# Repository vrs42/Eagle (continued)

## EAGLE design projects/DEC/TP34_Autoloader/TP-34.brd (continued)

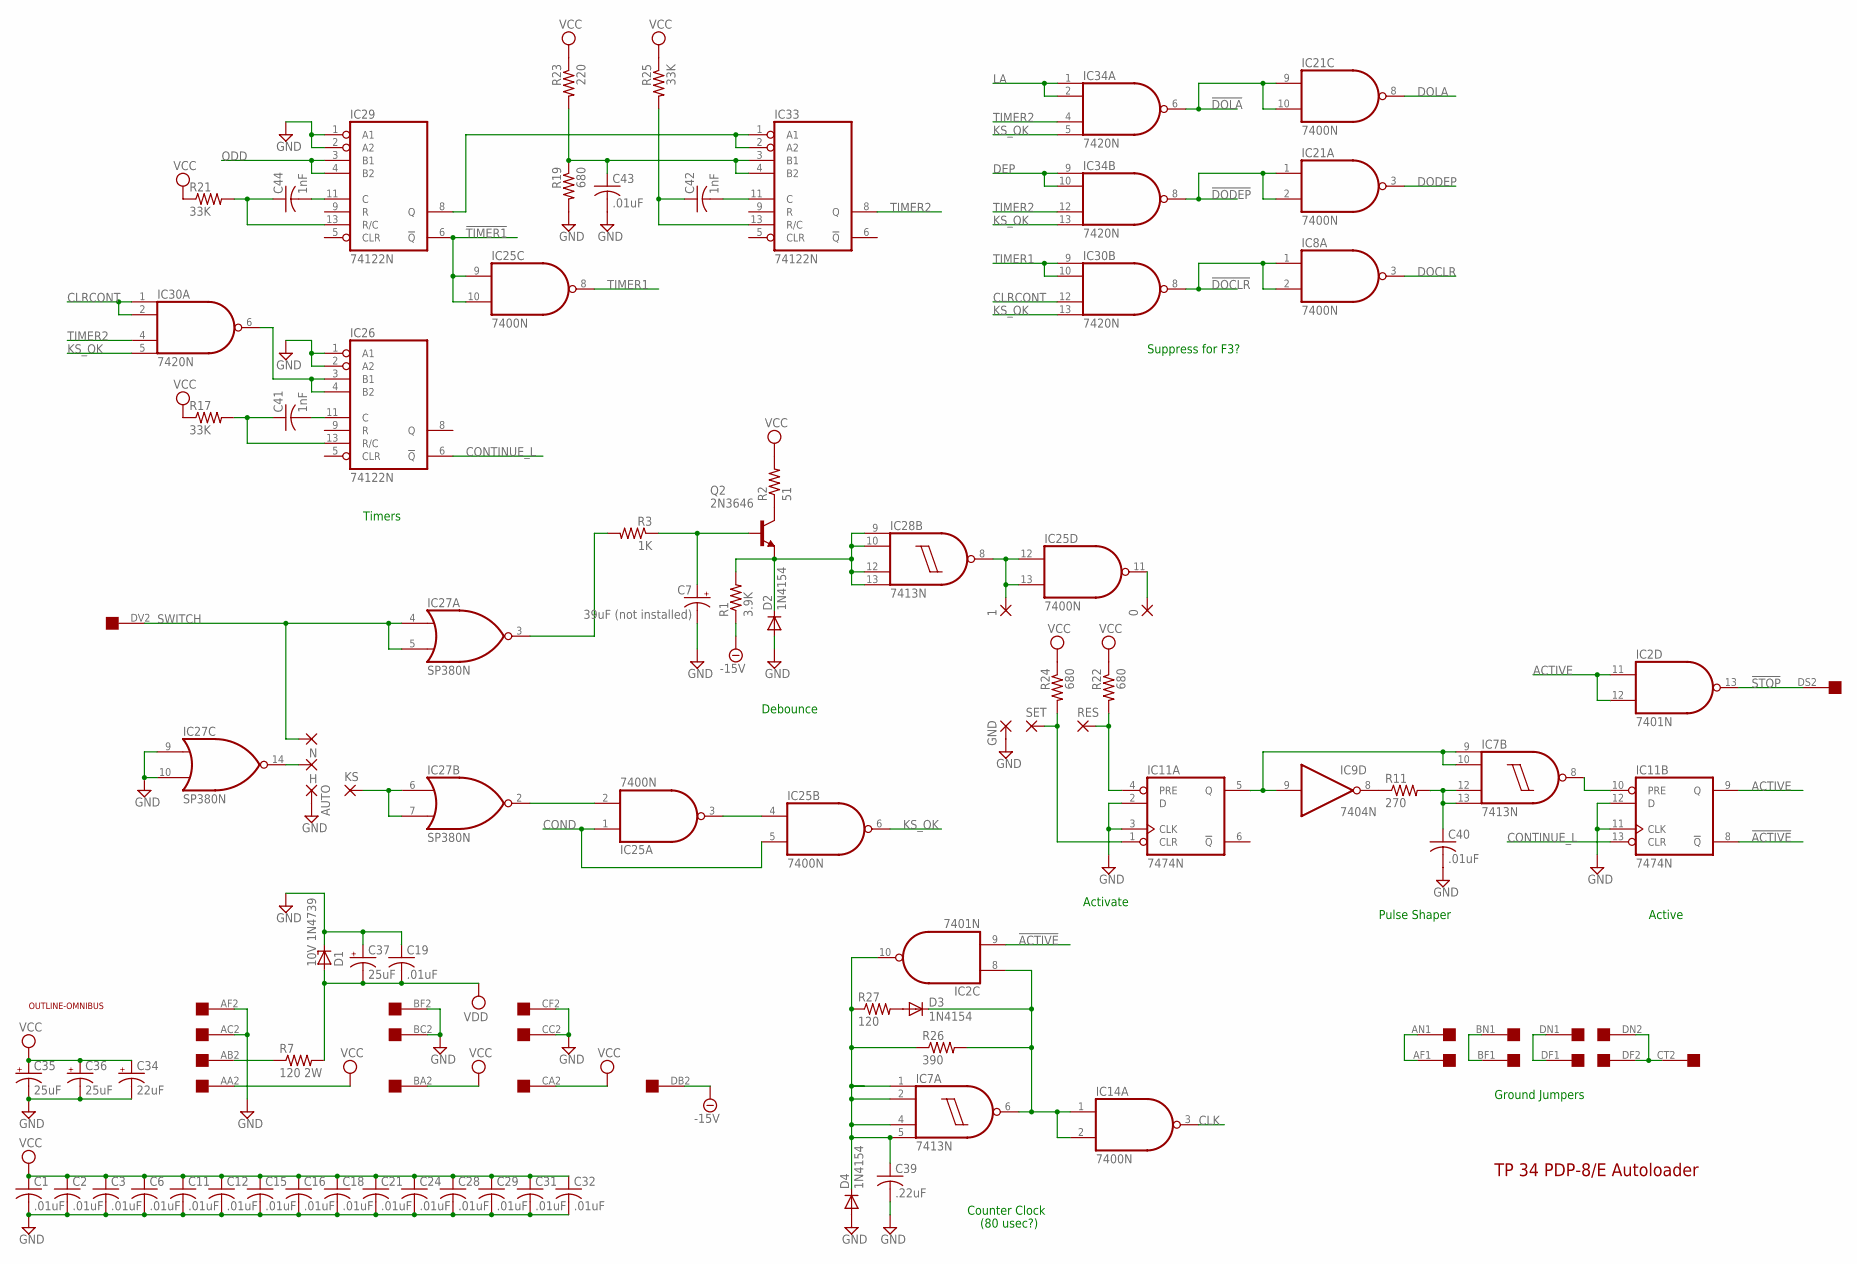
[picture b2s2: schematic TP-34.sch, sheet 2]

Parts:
0, 1: 1,6/0,8
AUTO: 1,6/0,8
C1, C2, C3, C6, C11, C12, C15, C16, C18, C19, C21, C24, C28, C29, C31, C32, C40, C43: .01uF; C075-032X103
C7: 39uF (not installed); E15-5
C34: 22uF; E12-8
C35, C36, C37: 25uF; E15-5
C39: .22uF; C075-032X103
C41, C42, C44: 1nF; C075-032X103
D1: 10V 1N4739; C1702-15
D2, D3, D4: 1N4154; DO35-10
GND: 1,6/0,8
H: 1,6/0,8
IC2: 7401N; DIL14
IC7, IC28: 7413N; DIL14
IC8, IC14, IC21, IC25: 7400N; DIL14
IC9: 7404N; DIL14
IC11: 7474N; DIL14
IC26, IC29, IC33: 74122N; DIL14
IC27: SP380N; DIL14
IC30, IC34: 7420N; DIL14
KS: 1,6/0,8
N: 1,6/0,8
Q2: 2N3646; TO5
R1: 3.9K; 0207/10
R2: 51; 0207/10
R3: 1K; 0207/10
R7: 120 2W; 0414/15
R11: 270; 0207/12
R17, R21, R25: 33K; 0207/10
R19, R22, R24: 680; 0207/10
R23: 220; 0207/10
R26: 390; 0207/10
R27: 120; 0207/10
RES: 1,6/0,8
SET: 1,6/0,8
U$1: OUTLINE-OMNIBUS; OMNIBUS
U$2: QUAD; EDGE-CON8

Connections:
!ACTIVE: IC2.9 (I1), IC11.8 (!Q); also elsewhere on the board
!DOCLR: IC8.1 (I0), IC8.2 (I1), IC30.8 (O); also elsewhere on the board
!DODEP: IC21.1 (I0), IC21.2 (I1), IC34.8 (O); also elsewhere on the board
!DOLA: IC21.9 (I0), IC21.10 (I1), IC34.6 (O); also elsewhere on the board
!STOP: IC2.13 (O), U$2.DS2
!TIMER1: IC25.9 (I0), IC25.10 (I1), IC29.6 (!Q)
-15V: R1.1, U$2.DB2
ACTIVE: IC2.11 (I0), IC2.12 (I1), IC11.9 (Q); also elsewhere on the board
CLK: IC14.3 (O); also elsewhere on the board
CLRCONT: IC30.1 (I0), IC30.2 (I1), IC30.12 (I2); also elsewhere on the board
COND: IC25.1 (I0), IC25.5 (I1); also elsewhere on the board
CONTINUE_L: IC11.13 (CLR), IC26.6 (!Q); also elsewhere on the board
DEP: IC34.9 (I0), IC34.10 (I1); also elsewhere on the board
DOCLR: IC8.3 (O); also elsewhere on the board
DODEP: IC21.3 (O); also elsewhere on the board
DOLA: IC21.8 (O); also elsewhere on the board
GND: AUTO.1, C1.2, C2.2, C3.2, C6.2, C7.-, C11.2, C12.2, C15.2, C16.2, C18.2, C19.1, C21.2, C24.2, C28.2, C29.2, C31.2, C32.2, C34.-, C35.-, C36.-, C37.+, C39.2, C40.2, C43.2, D1.C, D2.A, D4.A, GND.1, IC2.7 (GND), IC7.7 (GND), IC8.7 (GND), IC9.7 (GND), IC11.2 (D), IC11.3 (CLK), IC11.7 (GND), IC11.11 (CLK), IC11.12 (D), IC14.7 (GND), IC21.7 (GND), IC25.7 (GND), IC26.1 (A1), IC26.2 (A2), IC26.7 (GND), IC27.1 (GND), IC27.9 (I0), IC27.10 (I1), IC28.7 (GND), IC29.1 (A1), IC29.2 (A2), IC29.7 (GND), IC30.7 (GND), IC33.7 (GND), IC34.7 (GND), R19.2, U$2.AC2, U$2.AF2, U$2.BC2, U$2.BF2, U$2.CC2, U$2.CF2; also elsewhere on the board
KS_OK: IC25.6 (O), IC30.5 (I3), IC30.13 (I3), IC34.5 (I3), IC34.13 (I3)
LA: IC34.1 (I0), IC34.2 (I1); also elsewhere on the board
unnamed: U$2.AF1, U$2.AN1
unnamed: U$2.BF1, U$2.BN1
unnamed: U$2.DF1, U$2.DN1
unnamed: U$2.CT2, U$2.DF2, U$2.DN2
unnamed: D2.C, IC28.9 (I0), IC28.10 (I1), IC28.12 (I2), IC28.13 (I3), Q2.1 (E), R1.2
unnamed: D3.C, IC2.8 (I0), IC7.6 (O), IC14.1 (I0), IC14.2 (I1), R26.2
unnamed: D3.A, R27.2
unnamed: C39.1, D4.C, IC2.10 (O), IC7.1 (I0), IC7.2 (I1), IC7.4 (I2), IC7.5 (I3), R26.1, R27.1
unnamed: IC7.9 (I0), IC7.10 (I1), IC9.9 (I), IC11.5 (Q)
unnamed: 1.1, IC25.12 (I0), IC25.13 (I1), IC28.8 (O)
unnamed: IC11.4 (PRE), R22.2, RES.1
unnamed: IC11.1 (CLR), R24.2, SET.1
unnamed: 0.1, IC25.11 (O)
unnamed: C42.1, IC33.13 (R/C), R25.2
unnamed: C42.2, IC33.11 (C)
unnamed: C43.1, IC33.3 (B1), IC33.4 (B2), R19.1, R23.2
unnamed: C44.1, IC29.13 (R/C), R21.2
unnamed: C40.1, IC7.12 (I2), IC7.13 (I3), R11.2
unnamed: IC7.8 (O), IC11.10 (PRE)
unnamed: C44.2, IC29.11 (C)
unnamed: IC9.8 (O), R11.1
unnamed: C7.+, Q2.2 (B), R3.1
unnamed: Q2.3 (C), R2.1
unnamed: C41.1, IC26.13 (R/C), R17.2
unnamed: C41.2, IC26.11 (C)
unnamed: R7.1, U$2.AB2
unnamed: IC25.3 (O), IC25.4 (I0)
unnamed: IC25.2 (I1), IC27.2 (O)
unnamed: IC26.3 (B1), IC26.4 (B2), IC30.6 (O)
unnamed: IC27.6 (I0), IC27.7 (I1), KS.1
unnamed: H.1, IC27.14 (O)
unnamed: IC29.8 (Q), IC33.1 (A1), IC33.2 (A2)
ODD: IC29.3 (B1), IC29.4 (B2); also elsewhere on the board
SWITCH: IC27.4 (I0), IC27.5 (I1), N.1, U$2.DV2
SWITCHL: IC27.3 (O), R3.2
TIMER1: IC25.8 (O), IC30.9 (I0), IC30.10 (I1)
TIMER2: IC30.4 (I2), IC33.8 (Q), IC34.4 (I2), IC34.12 (I2)
VCC: C1.1, C2.1, C3.1, C6.1, C11.1, C12.1, C15.1, C16.1, C18.1, C21.1, C24.1, C28.1, C29.1, C31.1, C32.1, C34.+, C35.+, C36.+, IC2.14 (VCC), IC7.14 (VCC), IC8.14 (VCC), IC9.14 (VCC), IC11.14 (VCC), IC14.14 (VCC), IC21.14 (VCC), IC25.14 (VCC), IC26.14 (VCC), IC27.8 (VCC), IC28.14 (VCC), IC29.14 (VCC), IC30.14 (VCC), IC33.14 (VCC), IC34.14 (VCC), R2.2, R17.1, R21.1, R22.1, R23.1, R24.1, R25.1, U$2.AA2, U$2.BA2, U$2.CA2; also elsewhere on the board
VDD: C19.2, C37.-, D1.A, R7.2; also elsewhere on the board

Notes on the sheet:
TP 34 PDP-8/E Autoloader
Counter Clock
Pulse Shaper
Activate
Active
Ground Jumpers
Timers
Suppress for F3?
Debounce
(80 usec?)

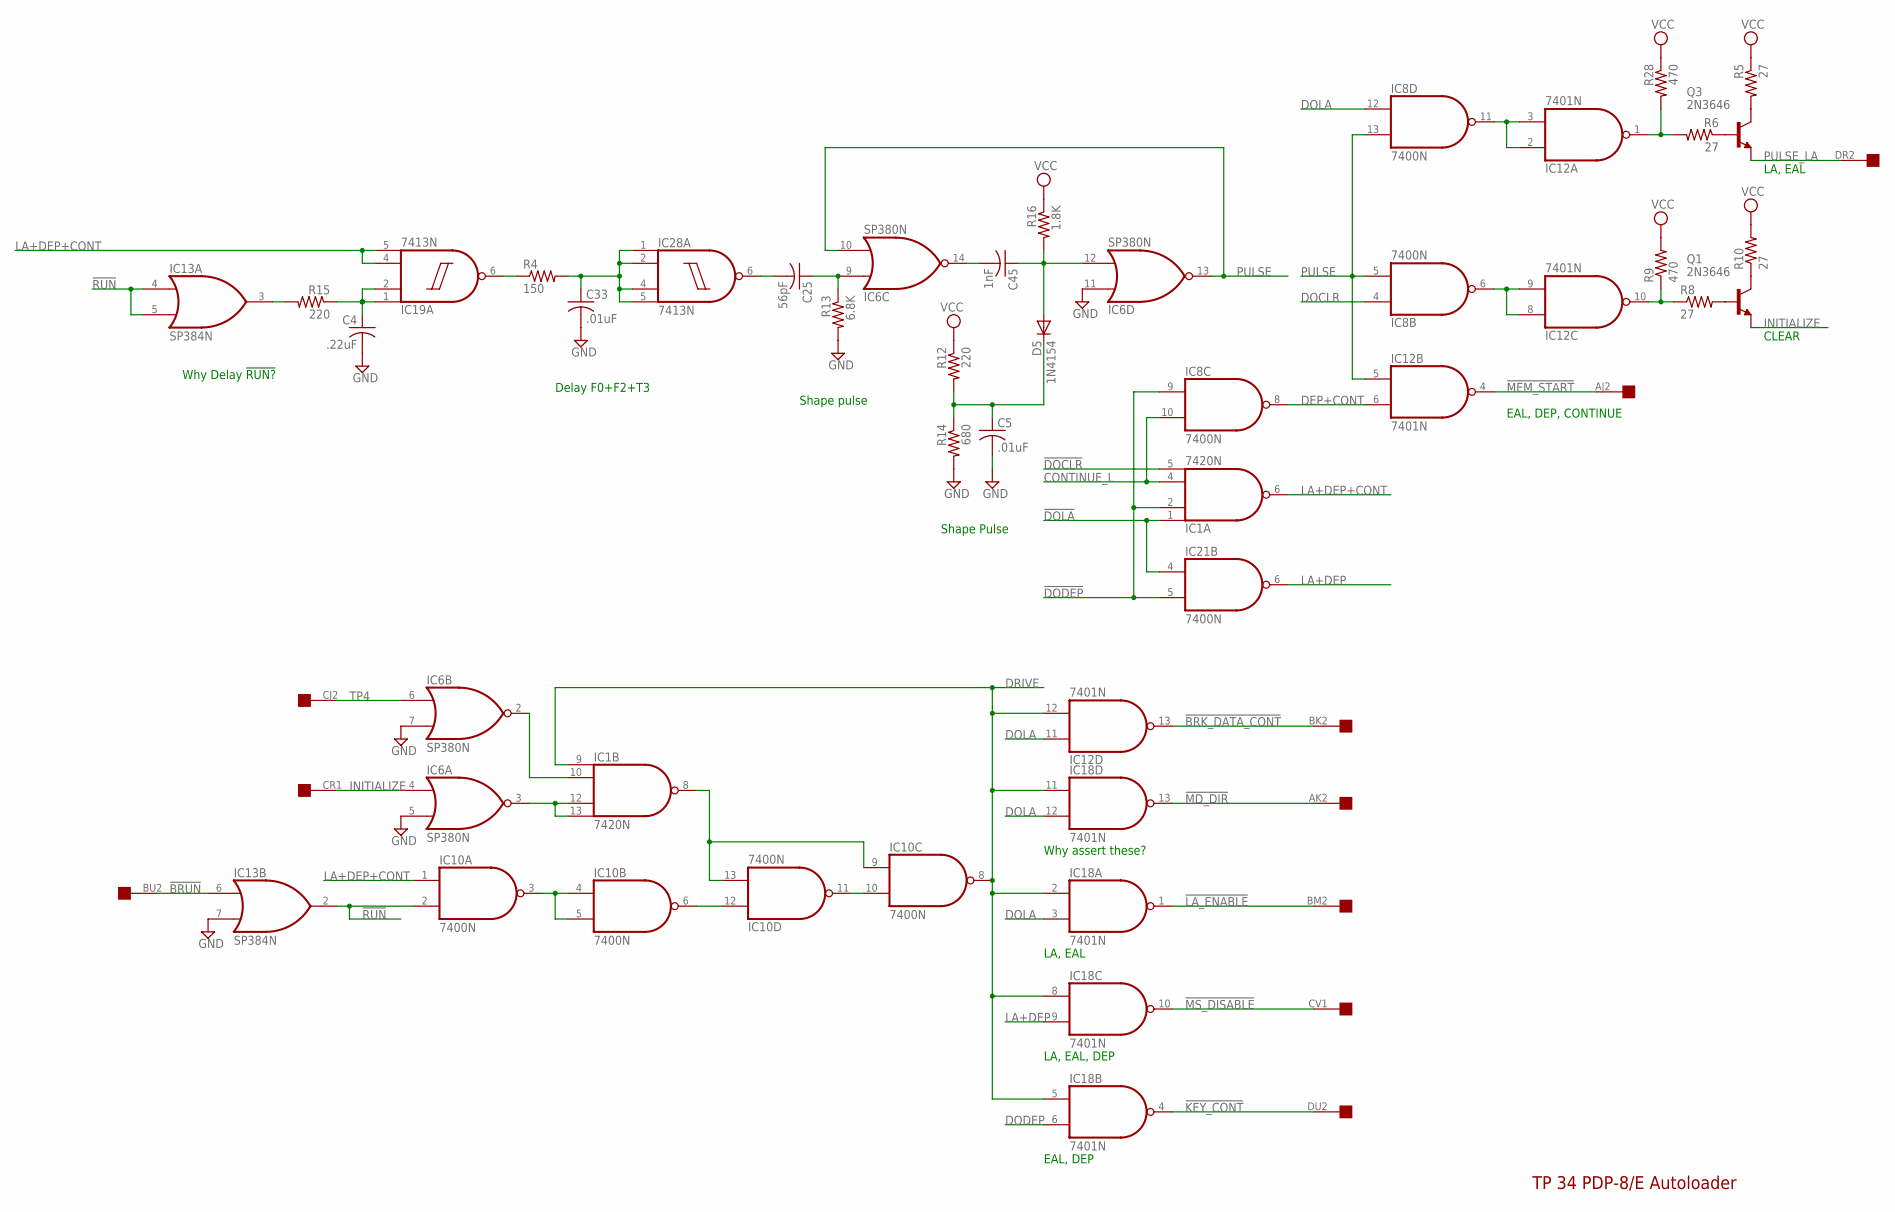
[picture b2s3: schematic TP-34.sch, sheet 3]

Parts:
C4: .22uF; C075-032X103
C5, C33: .01uF; C075-032X103
C25: 56pF; C102-043X133
C45: 1nF; C050-035X075
D5: 1N4154; DO35-10
IC1: 7420N; DIL14
IC6: SP380N; DIL14
IC8, IC10, IC21: 7400N; DIL14
IC12, IC18: 7401N; DIL14
IC13: SP384N; DIL14
IC19, IC28: 7413N; DIL14
Q1, Q3: 2N3646; TO5
R4: 150; 0207/10
R5, R6, R8, R10: 27; 0207/10
R9, R28: 470; 0207/10
R12: 220; 0207/10
R13: 6.8K; 0207/10
R14: 680; 0207/10
R15: 220; 0207/15
R16: 1.8K; 0207/10
U$2: QUAD; EDGE-CON8

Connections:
!BRK_DATA_CONT: IC12.13 (O), U$2.BK2
!BRUN: IC13.6 (I0), U$2.BU2
!DOCLR: IC1.5 (I3); also elsewhere on the board
!DODEP: IC1.2 (I1), IC8.9 (I0), IC21.5 (I1); also elsewhere on the board
!DOLA: IC1.1 (I0), IC21.4 (I0); also elsewhere on the board
!INITIALIZE: IC1.12 (I2), IC1.13 (I3), IC6.3 (O)
!KEY_CONT: IC18.4 (O), U$2.DU2
!LA_ENABLE: IC18.1 (O), U$2.BM2
!MD_DIR: IC18.13 (O), U$2.AK2
!MEM_START: IC12.4 (O), U$2.AJ2
!MS_DISABLE: IC18.10 (O), U$2.CV1
!RUN: IC10.2 (I1), IC13.2 (O), IC13.4 (I0), IC13.5 (I1)
!TP4: IC1.10 (I1), IC6.2 (O)
BRUNL: IC13.3 (O), R15.2
CONTINUE_L: IC1.4 (I2), IC8.10 (I1); also elsewhere on the board
DEP+CONT: IC8.8 (O), IC12.6 (I1)
DOCLR: IC8.4 (I0); also elsewhere on the board
DODEP: IC18.6 (I1); also elsewhere on the board
DOLA: IC8.12 (I0), IC12.11 (I0), IC18.3 (I1), IC18.12 (I1); also elsewhere on the board
DRIVE: IC1.9 (I0), IC10.8 (O), IC12.12 (I1), IC18.2 (I0), IC18.5 (I0), IC18.8 (I0), IC18.11 (I0); also elsewhere on the board
GND: C4.2, C5.2, C33.2, IC1.7 (GND), IC6.1 (GND), IC6.5 (I1), IC6.7 (I1), IC6.11 (I0), IC8.7 (GND), IC10.7 (GND), IC12.7 (GND), IC13.1 (GND), IC13.7 (I1), IC18.7 (GND), IC19.7 (GND), IC21.7 (GND), IC28.7 (GND), R13.2, R14.2; also elsewhere on the board
INITIALIZE: IC6.4 (I0), Q1.1 (E), U$2.CR1
LA+DEP: IC18.9 (I1), IC21.6 (O); also elsewhere on the board
LA+DEP+CONT: IC1.6 (O), IC10.1 (I0), IC19.4 (I2), IC19.5 (I3)
unnamed: IC10.6 (O), IC10.12 (I0)
unnamed: C25.2, IC28.6 (O)
unnamed: C25.1, IC6.9 (I0), R13.1
unnamed: C45.1, D5.A, IC6.12 (I1), R16.2
unnamed: C5.1, D5.C, R12.2, R14.1
unnamed: C45.2, IC6.14 (O)
unnamed: IC1.8 (O), IC10.9 (I0), IC10.13 (I1)
unnamed: IC8.11 (O), IC12.2 (I0), IC12.3 (I1)
unnamed: IC8.6 (O), IC12.8 (I0), IC12.9 (I1)
unnamed: IC10.3 (O), IC10.4 (I0), IC10.5 (I1)
unnamed: IC10.10 (I1), IC10.11 (O)
unnamed: IC12.1 (O), R6.2, R28.2
unnamed: IC12.10 (O), R8.1, R9.1
unnamed: Q1.3 (C), R10.1
unnamed: Q1.2 (B), R8.2
unnamed: C4.1, IC19.1 (I0), IC19.2 (I1), R15.1
unnamed: IC19.6 (O), R4.1
unnamed: C33.1, IC28.1 (I0), IC28.2 (I1), IC28.4 (I2), IC28.5 (I3), R4.2
unnamed: Q3.3 (C), R5.2
unnamed: Q3.2 (B), R6.1
PULSE: IC6.10 (I1), IC6.13 (O), IC8.5 (I1), IC8.13 (I1), IC12.5 (I0)
PULSE_LA: Q3.1 (E), U$2.DR2
TP4: IC6.6 (I0), U$2.CJ2
VCC: IC1.14 (VCC), IC6.8 (VCC), IC8.14 (VCC), IC10.14 (VCC), IC12.14 (VCC), IC13.8 (VCC), IC18.14 (VCC), IC19.14 (VCC), IC21.14 (VCC), IC28.14 (VCC), R5.1, R9.2, R10.2, R12.1, R16.1, R28.1; also elsewhere on the board

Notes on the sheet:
Why Delay !RUN?
Delay F0+F2+T3
Shape Pulse
TP 34 PDP-8/E Autoloader
Shape pulse
Why assert these?
LA, EAL
LA, EAL, DEP
EAL, DEP
CLEAR
EAL, DEP, CONTINUE

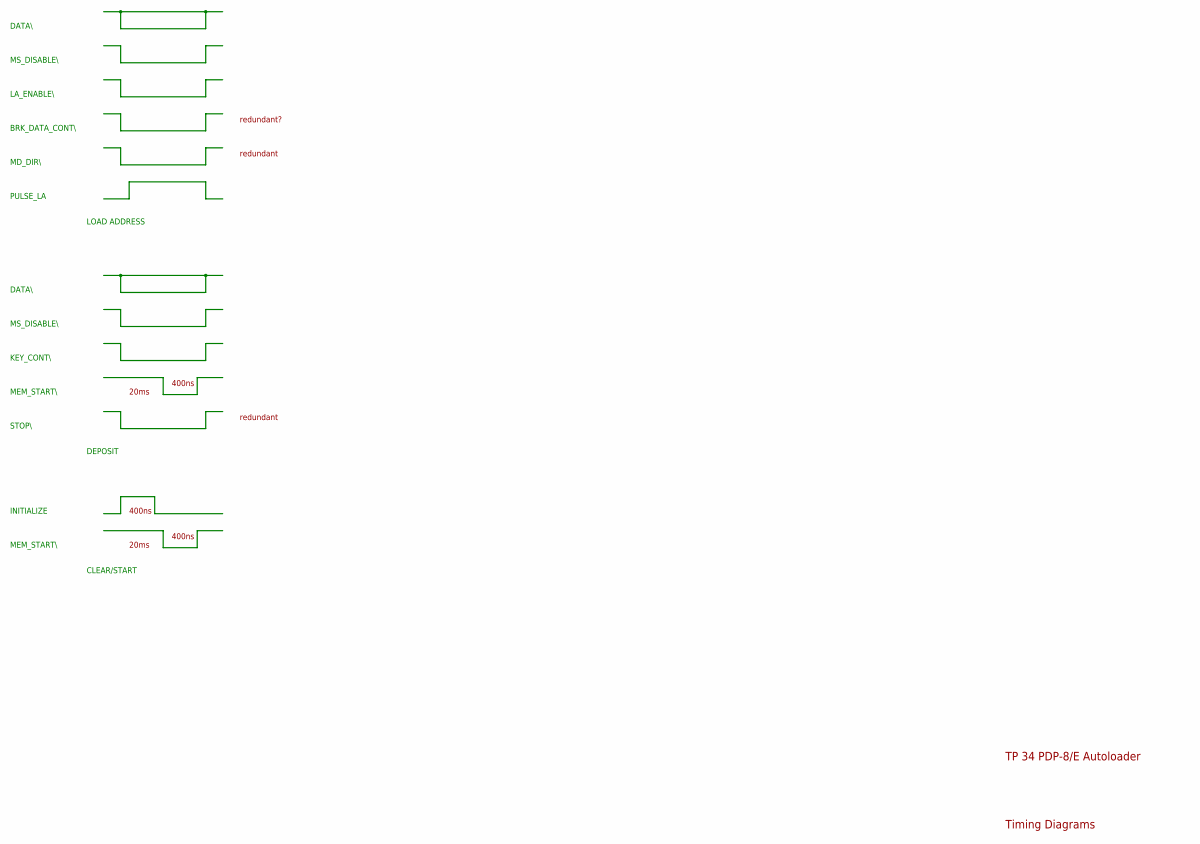
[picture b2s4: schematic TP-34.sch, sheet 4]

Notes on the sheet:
DATA\\
MS_DISABLE\\
BRK_DATA_CONT\\
MD_DIR\\
LOAD ADDRESS
MEM_START\\
KEY_CONT\\
DEPOSIT
PULSE_LA
STOP\\
INITIALIZE
TP 34 PDP-8/E Autoloader
Timing Diagrams
LA_ENABLE\\
CLEAR/START
redundant
20ms
400ns
redundant?

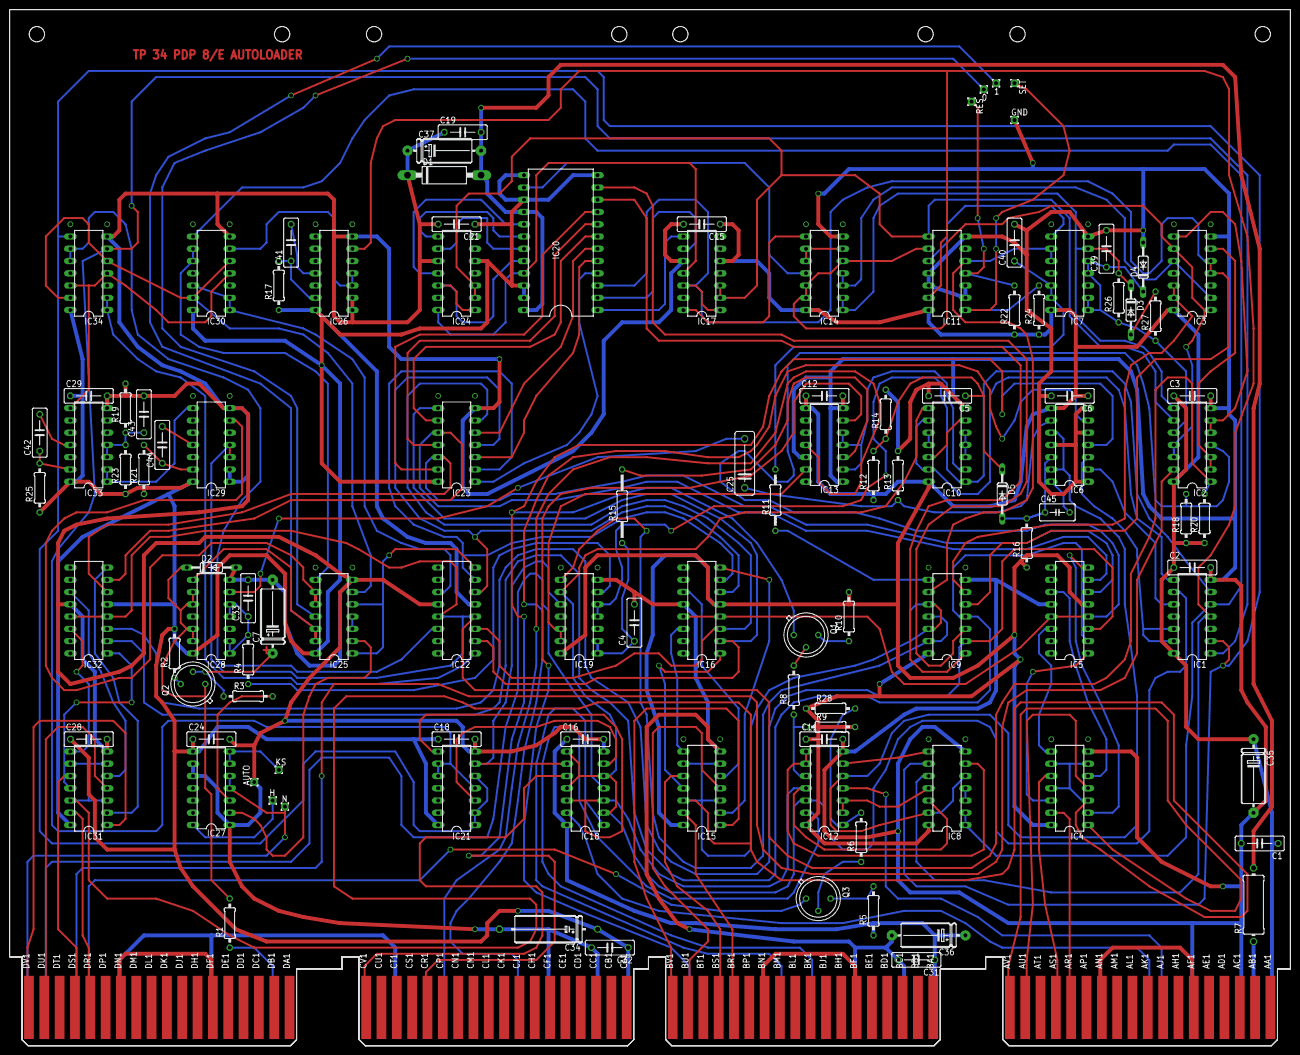
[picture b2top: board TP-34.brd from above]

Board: 2 copper layers, 265.3 x 214.6 mm, 113 parts (0 on the bottom side), 156 nets.
